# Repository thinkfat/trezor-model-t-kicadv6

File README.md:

# trezor-model-t-kicadv6

This is an adaptation of the official Trezor Model T PCB to KiCAD. 
It was created in response to an EEVBlog episode where Dave tested
whether releasing the PCB CAD files (instead of Gerber files) for 
an Open Hardware project was enough to actually recreate the PCB.

This is not a ready-to-manufacture project. It is also not identical
to the genuine Trezor T PCB. Several changes have been made by myself to
loosen the manufacturing constraints of the PCB and improve the routing
for EMC compliance.

This PCB has never been actually manufactured. Use it on your own risk 
as a starting point to make your own Trezor Model T.

I have neither plans or intention to continue this work.

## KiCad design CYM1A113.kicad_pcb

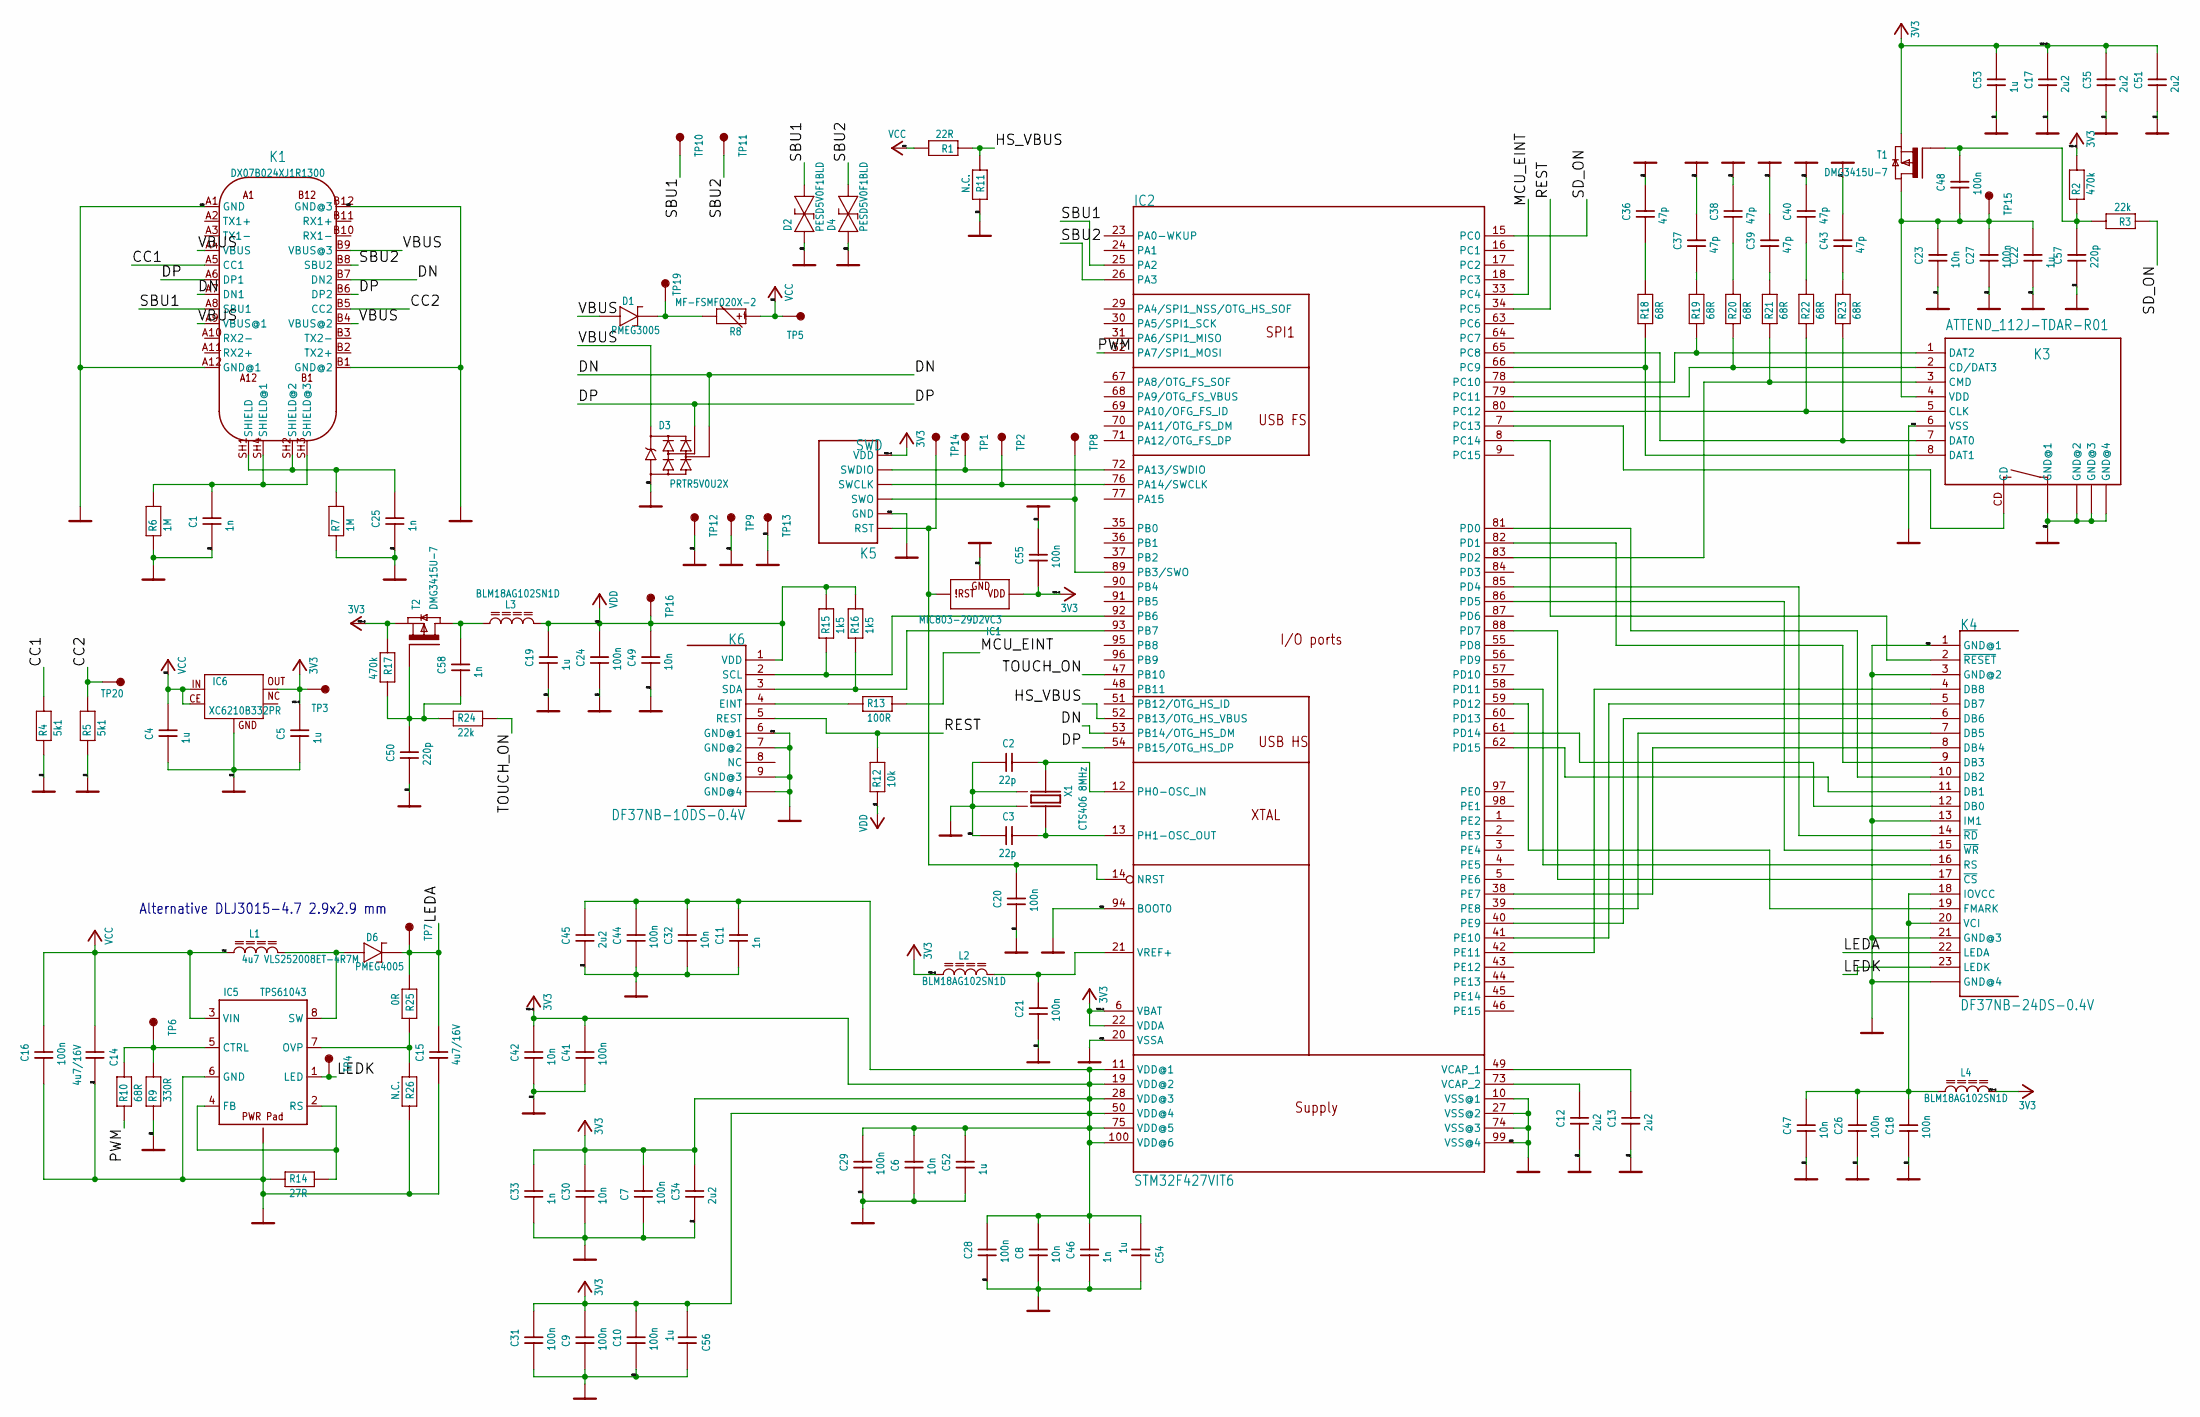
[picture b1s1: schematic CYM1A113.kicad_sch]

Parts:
C1, C11, C25, C33, C46, C58: 1n; 0402
C2, C3: 22p; 0402
C4, C19, C22, C52, C53, C54, C56: 1u; 0603_REFLOW
C5: 1u; 0603
C6, C8, C23, C30, C32, C42, C47, C49: 10n; 0402
C7, C9, C10, C16, C18, C20, C21, C24, C26, C27, C28, C29, C31, C41, C44, C48, C55: 100n; 0402
C12, C13, C17, C34, C35, C45, C51: 2u2; 0805_REFLOW
C14, C15: 4u7/16V; 0805_REFLOW
C36, C37, C38, C39, C40, C43: 47p; 0402
C50, C57: 220p; 0402
D1: PMEG3005; SOD323F
D2, D4: PESD5V0F1BLD; SOD882D
D3: PRTR5V0U2X; SOT143B_REFLOW
D6: PMEG4005; SOD323F
IC1: MIC803-29D2VC3; SOT23_MEDIUM_SIZE
IC2: STM32F427VIT6; LQFP100_NO_CENTER_NO_TDOCU
IC5: TPS61043; WSON-8_3X3MM
IC6: XC6210B332PR; SOT89-5
K1: DX07B024XJ1R1300; USB_C_JAE_DX07B024XJ1
K3: ATTEND_112J-TDAR-R01; ATTEND_112J-TXAR-R01_SMALL
K4: DF37NB-24DS-0.4V
K5: SWD
K6: DF37NB-10DS-0.4V
L1: 4u7 VLS252008ET-4R7M; L_2.5X2.0
L2, L3, L4: BLM18AG102SN1D; 0603_REFLOW
R1: 22R; 0402
R2, R17: 470k; 0402
R3, R24: 22k; 0402
R4, R5: 5k1; 0402
R6, R7: 1M; 0402
R8: MF-FSMF020X-2; 0603
R9: 330R; 0402
R10, R18, R19, R20, R21, R22, R23: 68R; 0402
R11, R26: N.C.; 0402
R12: 10k; 0402
R13: 100R; 0402
R14: 27R; 0402
R15, R16: 1k5; 0402
R25: 0R; 0402
T1, T2: DMG3415U-7; SOT23_REFLOW
TP1, TP2, TP4, TP6, TP7, TP8, TP9, TP12, TP13, TP14, TP15, TP16: MB_1.27; MB1.27
TP3, TP5, TP10, TP11: MB_1.50; MB1.5
TP19, TP20: MB_1.00
X1: CTS406 8MHz; X6,0X3,5

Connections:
/CC1: K1.A5 (CC1), R4.P$2 (2)
/CC2: K1.B5 (CC2), R5.P$2 (2), TP20.1
/DN: D3.3 (I/O2), IC2.53 (PB14/OTG_HS_DM), K1.A7 (DN1), K1.B7 (DN2)
/DP: D3.2 (I/O1), IC2.54 (PB15/OTG_HS_DP), K1.A6 (DP1), K1.B6 (DP2)
/HS_VBUS: IC2.52 (PB13/OTG_HS_VBUS), R1.P$1 (1), R11.P$1 (1)
/LEDA: C15.2, D6.K (2), K4.22 (LEDA), R25.P$1 (1), TP7.1
/LEDK: IC5.1 (LED), K4.23 (LEDK), TP4.1
/MCU_EINT: IC2.33 (PC4), R13.P$2 (2)
/PWM: IC2.32 (PA7/SPI1_MOSI), R10.P$1 (1)
/REST: IC2.34 (PC5), K6.5 (REST), R12.P$2 (2)
/SBU1: D2.2, IC2.25 (PA2), K1.A8 (SBU1), TP10.1
/SBU2: D4.2, IC2.26 (PA3), K1.B8 (SBU2), TP11.1
/SD_ON: IC2.15 (PC0), R3.P$1 (1)
/TOUCH_ON: IC2.47 (PB10), R24.P$2 (2)
/VBUS: D1.A (1), D3.4 (VCC), K1.A4 (VBUS), K1.A9 (VBUS@1), K1.B4 (VBUS@2), K1.B9 (VBUS@3)
GND: C1.P$1 (1), C2.P$1 (1), C3.P$1 (1), C4.1, C5.1, C6.P$1 (1), C7.P$1 (1), C8.P$1 (1), C9.P$1 (1), C10.P$1 (1), C11.P$1 (1), C12.1, C13.1, C14.2, C15.1, C16.P$1 (1), C17.1, C18.P$1 (1), C19.1, C20.P$1 (1), C21.P$1 (1), C22.1, C23.P$1 (1), C24.P$1 (1), C25.P$1 (1), C26.P$1 (1), C27.P$1 (1), C28.P$1 (1), C29.P$1 (1), C30.P$1 (1), C31.P$1 (1), C32.P$1 (1), C33.P$1 (1), C34.1, C35.1, C36.P$2 (2), C37.P$2 (2), C38.P$2 (2), C39.P$2 (2), C40.P$2 (2), C41.P$1 (1), C42.P$1 (1), C43.P$2 (2), C44.P$1 (1), C45.1, C46.P$1 (1), C47.P$1 (1), C49.P$1 (1), C50.P$1 (1), C51.1, C52.1, C53.1, C54.2, C55.P$2 (2), C56.2, C57.P$1 (1), D2.1, D3.1 (GND), D4.1, IC1.1 (GND), IC2.10 (VSS@1), IC2.20 (VSSA), IC2.27 (VSS@2), IC2.74 (VSS@3), IC2.94 (BOOT0), IC2.99 (VSS@4), IC5.6 (GND), IC5.EP, IC5.EP$1 (EP), IC5.EP$2 (EP), IC5.EP$3 (EP), IC5.EP$4 (EP), IC6.2 (GND), K1.A1 (GND), K1.A12 (GND@1), K1.B1 (GND@2), K1.B12 (GND@3), K3.6 (VSS), K3.GND@1, K3.GND@2, K3.GND@3, K3.GND@4, K4.1 (GND@1), K4.3 (GND@2), K4.13 (IM1), K4.21 (GND@3), K4.24 (GND@4), K4.25 (GND@4), K4.26 (GND@4), K5.GND, K6.6 (GND@1), K6.7 (GND@2), K6.9 (GND@3), K6.10 (GND@4), K6.11 (GND@4), K6.12 (GND@4), R4.P$1 (1), R5.P$1 (1), R6.P$1 (1), R7.P$1 (1), R9.P$1 (1), R11.P$2 (2), R14.P$1 (1), R26.P$2 (2), TP9.1, TP12.1, TP13.1, X1.2 (GND1), X1.4 (GND2)
unnamed: C1.P$2 (2), K1.SH3 (SHIELD@3), K1.SH4 (SHIELD@1), R6.P$2 (2)
unnamed: C2.P$2 (2), IC2.12 (PH0-OSC_IN), X1.1
unnamed: C3.P$2 (2), IC2.13 (PH1-OSC_OUT), X1.3 (2)
unnamed: C12.2, IC2.73 (VCAP_2)
unnamed: C13.2, IC2.49 (VCAP_1)
unnamed: C18.P$2 (2), C26.P$2 (2), C47.P$2 (2), K4.18 (IOVCC), K4.20 (VCI), L4.1
unnamed: C20.P$2 (2), IC1.2 (RES), IC2.14 (NRST), K5.RST, TP14.1
unnamed: C21.P$2 (2), IC2.21 (VREF+), L2.2
unnamed: C22.2, C23.P$2 (2), C27.P$2 (2), C48.P$1 (1), K3.4 (VDD), T1.3 (D), TP15.1
unnamed: C25.P$2 (2), K1.SH1 (SHIELD), K1.SH2 (SHIELD@2), R7.P$2 (2)
unnamed: C36.P$1 (1), R18.P$2 (2)
unnamed: C37.P$1 (1), R19.P$2 (2)
unnamed: C38.P$1 (1), R20.P$2 (2)
unnamed: C39.P$1 (1), R21.P$2 (2)
unnamed: C40.P$1 (1), R22.P$2 (2)
unnamed: C43.P$1 (1), R23.P$2 (2)
unnamed: C48.P$2 (2), C57.P$2 (2), R2.P$1 (1), R3.P$2 (2), T1.2 (G)
unnamed: C50.P$2 (2), C58.P$1 (1), R17.P$2 (2), R24.P$1 (1), T2.2 (G)
unnamed: C58.P$2 (2), L3.1, T2.3 (D)
unnamed: D1.K (2), R8.2, TP19.1
unnamed: D6.A (1), IC5.8 (SW), L1.2
unnamed: IC2.7 (PC13), K3.CD
unnamed: IC2.8 (PC14), K4.2 (~RESET)
unnamed: IC2.38 (PE7), K4.8 (DB4)
unnamed: IC2.39 (PE8), K4.7 (DB5)
unnamed: IC2.40 (PE9), K4.6 (DB6)
unnamed: IC2.41 (PE10), K4.5 (DB7)
unnamed: IC2.42 (PE11), K4.4 (DB8)
unnamed: IC2.58 (PD11), K4.16 (RS)
unnamed: IC2.59 (PD12), K4.19 (FMARK)
unnamed: IC2.61 (PD14), K4.12 (DB0)
unnamed: IC2.62 (PD15), K4.11 (DB1)
unnamed: IC2.65 (PC8), K3.7 (DAT0), R23.P$1 (1)
unnamed: IC2.66 (PC9), K3.8 (DAT1), R18.P$1 (1)
unnamed: IC2.72 (PA13/SWDIO), K5.SWDIO, TP1.1
unnamed: IC2.76 (PA14/SWCLK), K5.SWCLK, TP2.1
unnamed: IC2.78 (PC10), K3.1 (DAT2), R19.P$1 (1)
unnamed: IC2.79 (PC11), K3.2 (CD/DAT3), R20.P$1 (1)
unnamed: IC2.80 (PC12), K3.5 (CLK), R22.P$1 (1)
unnamed: IC2.81 (PD0), K4.10 (DB2)
unnamed: IC2.82 (PD1), K4.9 (DB3)
unnamed: IC2.83 (PD2), K3.3 (CMD), R21.P$1 (1)
unnamed: IC2.85 (PD4), K4.14 (~RD)
unnamed: IC2.86 (PD5), K4.15 (~WR)
unnamed: IC2.88 (PD7), K4.17 (~CS)
unnamed: IC2.89 (PB3/SWO), K5.SWO, TP8.1
unnamed: IC2.92 (PB6), K6.2 (SCL), R15.P$1 (1)
unnamed: IC2.93 (PB7), K6.3 (SDA), R16.P$1 (1)
unnamed: IC5.2 (RS), IC5.4 (FB), R14.P$2 (2)
unnamed: IC5.5 (CTRL), R9.P$2 (2), R10.P$2 (2), TP6.1
unnamed: IC5.7 (OVP), R25.P$2 (2), R26.P$1 (1)
unnamed: K6.4 (EINT), R13.P$1 (1)
VBAT: C19.2, C24.P$2 (2), C49.P$2 (2), K6.1 (VDD), L3.2, R12.P$1 (1), R15.P$2 (2), R16.P$2 (2), TP16.1
VCC: C4.2, C14.1, C16.P$2 (2), IC5.3 (VIN), IC6.1 (CE), IC6.4 (IN), L1.1, R1.P$2 (2), R8.1, TP5.1
VCC-2: C5.2, C6.P$2 (2), C7.P$2 (2), C8.P$2 (2), C9.P$2 (2), C10.P$2 (2), C11.P$2 (2), C17.2, C28.P$2 (2), C29.P$2 (2), C30.P$2 (2), C31.P$2 (2), C32.P$2 (2), C33.P$2 (2), C34.2, C35.2, C41.P$2 (2), C42.P$2 (2), C44.P$2 (2), C45.2, C46.P$2 (2), C51.2, C52.2, C53.2, C54.1, C55.P$1 (1), C56.1, IC1.3 (VDD), IC2.6 (VBAT), IC2.11 (VDD@1), IC2.19 (VDD@2), IC2.22 (VDDA), IC2.28 (VDD@3), IC2.50 (VDD@4), IC2.75 (VDD@5), IC2.100 (VDD@6), IC6.5 (OUT), K5.VCC (VDD), L2.1, L4.2, R2.P$2 (2), R17.P$1 (1), T1.1 (S), T2.1 (S), TP3.1

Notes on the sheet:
Alternative DLJ3015-4.7 2.9x2.9 mm

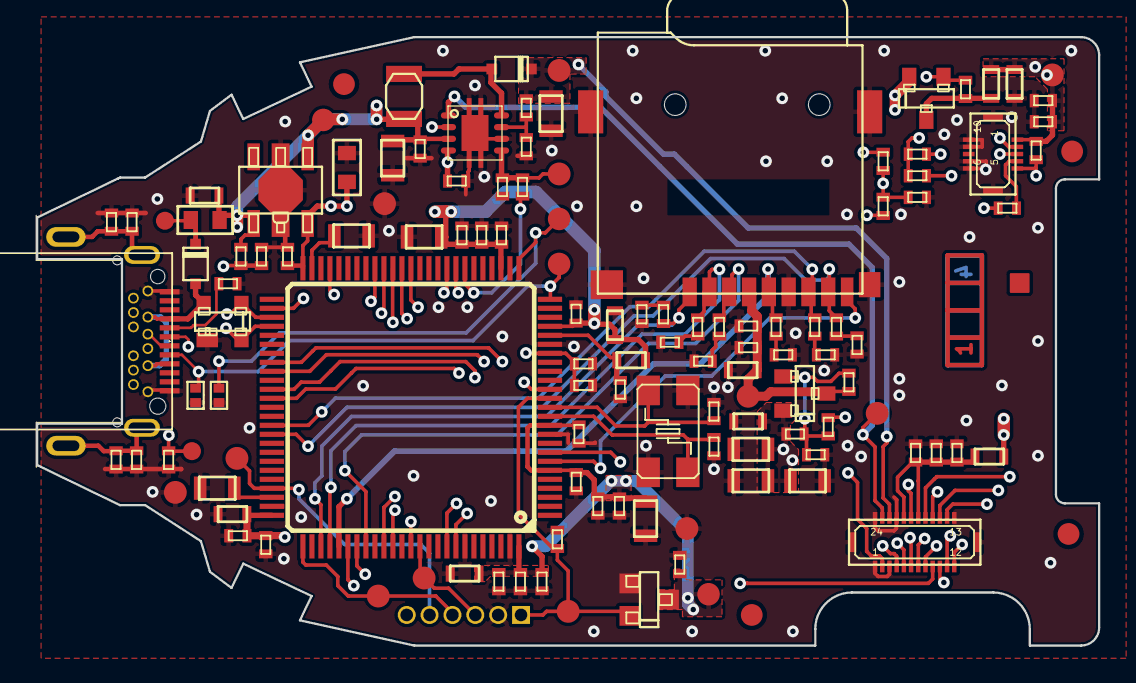
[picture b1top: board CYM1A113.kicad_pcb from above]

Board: 4 copper layers, 59.0 x 33.8 mm, 123 parts (0 on the bottom side), 71 nets.

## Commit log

2021-02-12 Initial commit of Trezor Model T schematics and PCB
    Imported from the original Eagle project files
    Cleanup of footprints and vias
    Setup of design rules to match the board
2021-02-13 Get rid of blind and micro vias
    Use regular through-vias, there's no need to go "micro" or even blind
    Add manufactoring constraings matching JLCPCB 4-layer process.
    All DRC violations resolved except around the USB-C receptacle. The
    chosen part doesn't fit into JLCPCBs capabilities due to hole-hole
    and hole-copper constraints.
2021-02-13 Routing improvements.
    Move the display traces away from the first inner layer to
    keep it as an unbroken ground plane. This eliminates most of the
    jumper traces, still using the first inner layer as reference plane
    for display and touchscreen signal.
